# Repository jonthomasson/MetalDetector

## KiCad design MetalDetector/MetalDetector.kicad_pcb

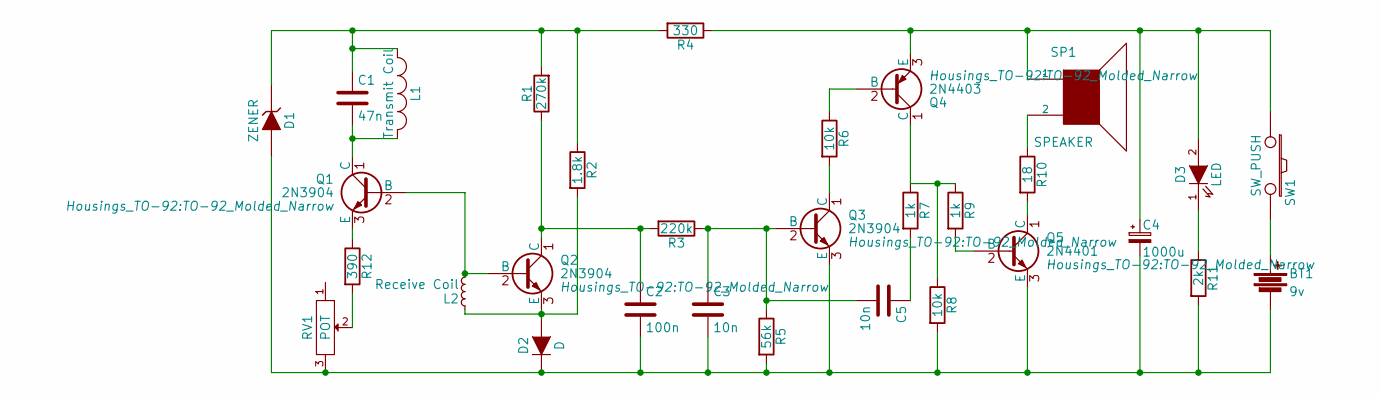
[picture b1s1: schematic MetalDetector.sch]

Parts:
BT1: 9v; C_Disc_D3_P2.5
C1: 47n; C_Disc_D3_P2.5
C2: 100n; C_Disc_D3_P2.5
C3, C5: 10n; C_Disc_D3_P2.5
C4: 1000u; Elko_vert_11.5x8mm_RM3.5
D1: ZENER; Diode_P600_Vertical_KathodeUp
D2: D; Diode_P600_Vertical_KathodeUp
D3: LED; LED-5MM
L1: Transmit Coil; C_Disc_D3_P2.5
L2: Receive Coil; C_Disc_D3_P2.5
Q1, Q2, Q3: 2N3904; TO-92_Molded_Narrow
Q4: 2N4403; TO-92_Molded_Narrow
Q5: 2N4401; TO-92_Molded_Narrow
R1: 270k; Resistor_Vertical_RM2_5mm
R2: 1.8k; Resistor_Vertical_RM2_5mm
R3: 220k; Resistor_Vertical_RM2_5mm
R4: 330; Resistor_Vertical_RM2_5mm
R5: 56k; Resistor_Vertical_RM2_5mm
R6, R8: 10k; Resistor_Vertical_RM2_5mm
R7, R9: 1k; Resistor_Vertical_RM2_5mm
R10: 18; Resistor_Vertical_RM2_5mm
R11: 2k; Resistor_Vertical_RM2_5mm
R12: 390; Resistor_Vertical_RM2_5mm
RV1: POT; Potentiometer_WirePads_Small
SP1: SPEAKER; C_Disc_D3_P2.5
SW1: SW_PUSH; SS_12D07_SWITCH

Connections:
unnamed: BT1.1, SW1.2
unnamed: BT1.2, C2.2, C3.2, C4.2, D1.2 (A), D2.1 (K), Q3.3 (E), Q5.3 (E), R5.2, R8.2, R11.2, RV1.3
unnamed: C1.1, D1.1 (K), L1.1, R1.2, R2.1, R4.2
unnamed: C1.2, L1.2, Q1.1 (C)
unnamed: C2.1, Q2.1 (C), R1.1, R3.2
unnamed: C3.1, C5.2, Q3.2 (B), R3.1, R5.1
unnamed: C4.1, D3.2 (A), Q4.3 (E), R4.1, SP1.1, SW1.1
unnamed: C5.1, R7.2
unnamed: D2.2 (A), L2.1, Q2.3 (E), R2.2
unnamed: D3.1 (K), R11.1
unnamed: L2.2, Q1.2 (B), Q2.2 (B)
unnamed: Q1.3 (E), R12.1
unnamed: Q3.1 (C), R6.2
unnamed: Q4.1 (C), R7.1, R8.1, R9.1
unnamed: Q4.2 (B), R6.1
unnamed: Q5.1 (C), R10.2
unnamed: Q5.2 (B), R9.2
unnamed: R10.1, SP1.2
unnamed: R12.2, RV1.2

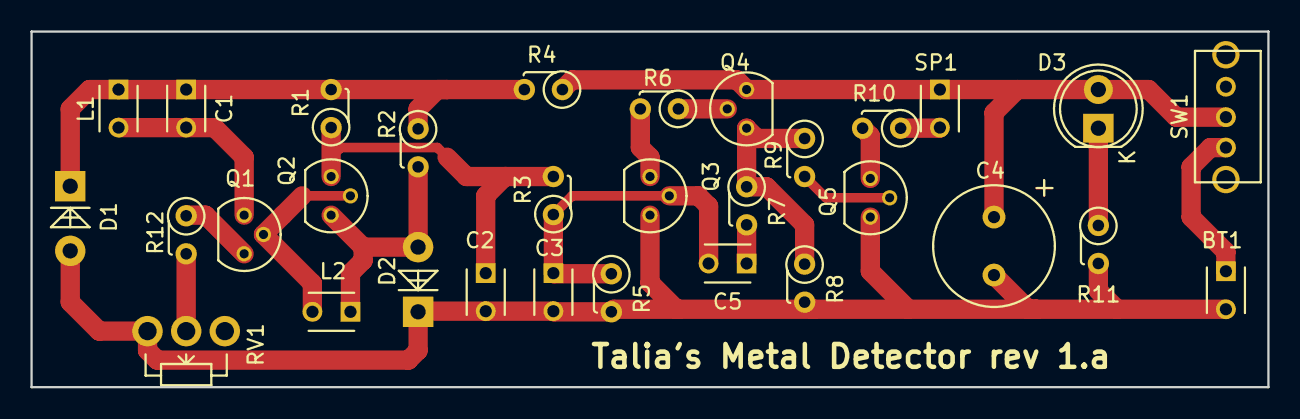
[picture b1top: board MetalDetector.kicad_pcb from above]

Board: 2 copper layers, 81.3 x 23.4 mm, 31 parts (0 on the bottom side), 19 nets.

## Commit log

2015-11-22 :octocat: Added .gitattributes & .gitignore files
2015-11-22 Initial Checkin
